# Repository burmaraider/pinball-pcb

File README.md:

# Pinball PCB's - Free to all

# What is this?

These boards are getting hard to find, so they should be availiable for people to build themselves.

## Board List

- A-15430 (10 Opto Board)
- 
- more coming soon...

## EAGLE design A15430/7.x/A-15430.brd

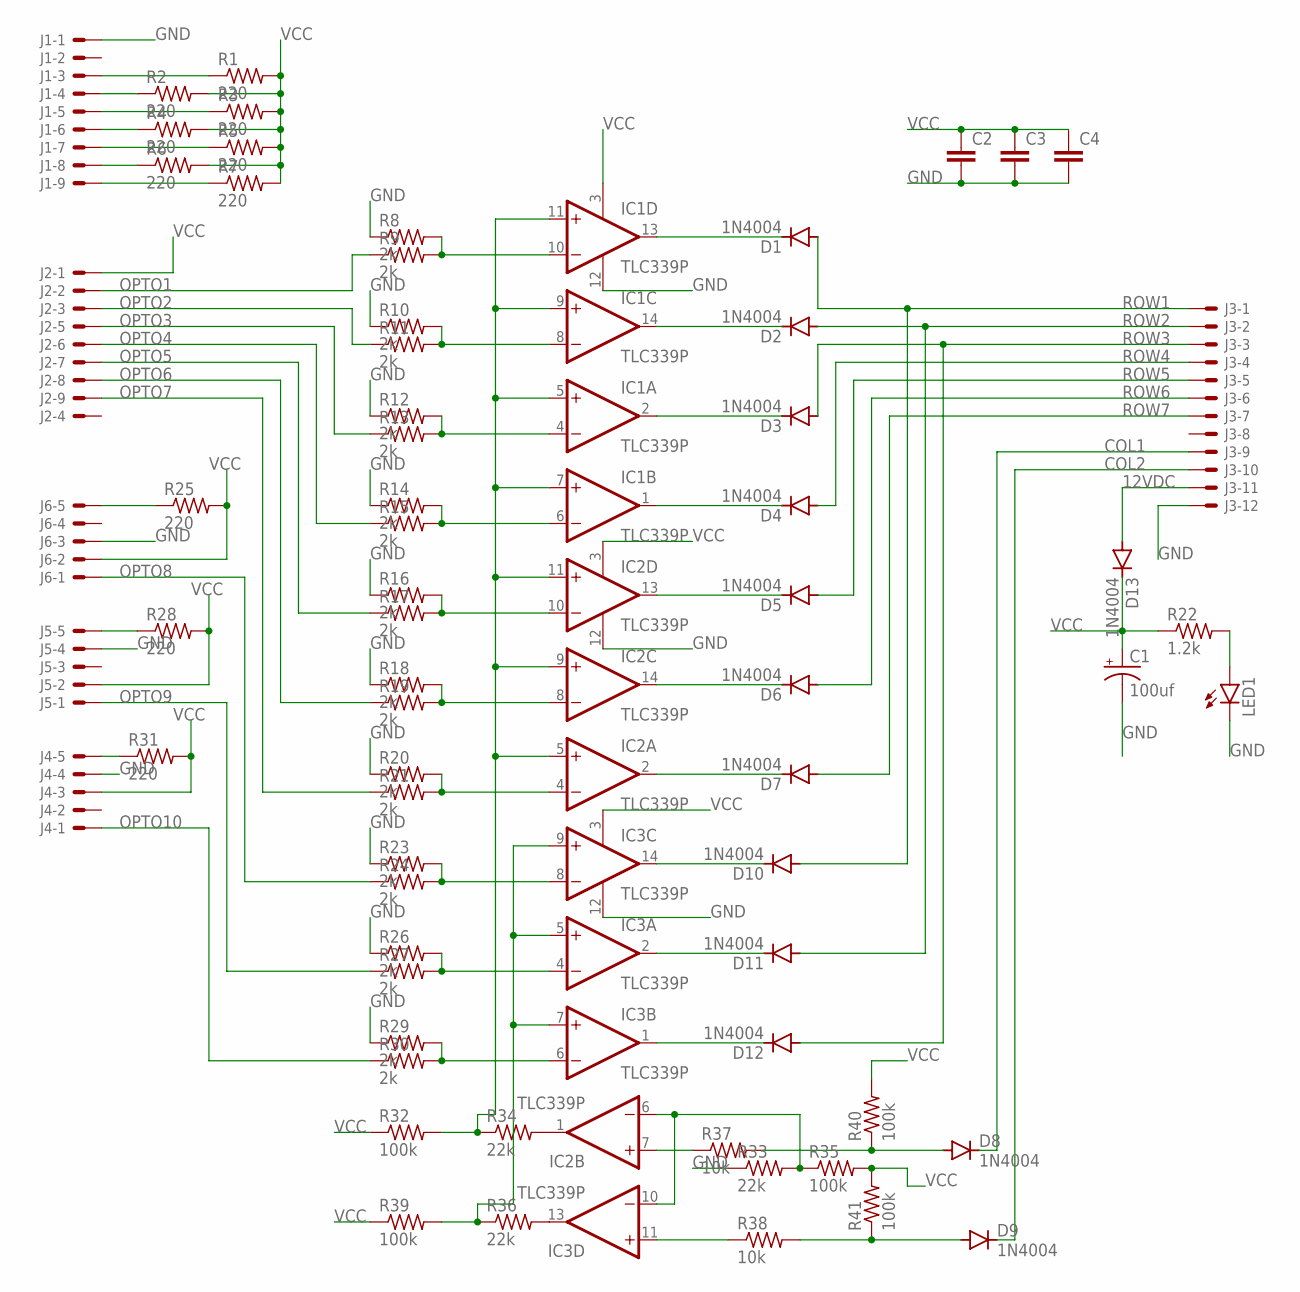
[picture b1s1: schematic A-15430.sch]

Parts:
C1: 100uf; E2,5-5
C2, C3, C4: C2.5/4; C2.5-4
D1, D2, D3, D4, D5, D6, D7, D8, D9, D10, D11, D12, D13: 1N4004; DO41-10
IC1, IC2, IC3: TLC339P; DIL14
J1, J2: KK-156-9
J3: KK-156-12
J4, J5, J6: KK-156-5
LED1: LED5MM
R1, R2, R3, R4, R5, R6, R7, R25, R28, R31: 220; 0617/22
R8, R9, R10, R11, R12, R13, R14, R15, R16, R17, R18, R19, R20, R21, R23, R24, R26, R27, R29, R30: 2k; 0207/10
R22: 1.2k; 0207/10
R32, R35, R39, R40, R41: 100k; 0207/10
R33, R34, R36: 22k; 0207/10
R37, R38: 10k; 0207/10

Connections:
12VDC: D13.A, J3.11
COL1: D8.C, J3.9
COL2: D9.C, J3.10
GND: C1.-, C2.2, C3.2, C4.2, IC1.12 (V-), IC2.12 (V-), IC3.12 (V-), J1.1, J3.12, J4.4, J5.4, J6.3, LED1.K (C), R8.1, R10.1, R12.1, R14.1, R16.1, R18.1, R20.1, R23.1, R26.1, R29.1, R33.1
unnamed: D1.C, IC1.13 (OUT)
unnamed: D2.C, IC1.14 (OUT)
unnamed: D3.C, IC1.2 (OUT)
unnamed: D4.C, IC1.1 (OUT)
unnamed: J6.5, R25.1
unnamed: LED1.A, R22.2
unnamed: J1.3, R1.1
unnamed: D5.C, IC2.13 (OUT)
unnamed: J1.4, R2.1
unnamed: J1.5, R3.1
unnamed: D6.C, IC2.14 (OUT)
unnamed: J1.6, R4.1
unnamed: D7.C, IC2.2 (OUT)
unnamed: J1.7, R5.1
unnamed: J1.8, R6.1
unnamed: IC1.10 (-IN), R8.2, R9.2
unnamed: IC1.8 (-IN), R10.2, R11.2
unnamed: IC1.4 (-IN), R12.2, R13.2
unnamed: IC1.6 (-IN), R14.2, R15.2
unnamed: IC2.10 (-IN), R16.2, R17.2
unnamed: IC2.8 (-IN), R18.2, R19.2
unnamed: IC2.4 (-IN), R20.2, R21.2
unnamed: IC3.8 (-IN), R23.2, R24.2
unnamed: IC3.4 (-IN), R26.2, R27.2
unnamed: IC3.6 (-IN), R29.2, R30.2
unnamed: IC2.6 (-IN), IC3.10 (-IN), R33.2, R35.1
unnamed: D10.C, IC3.14 (OUT)
unnamed: D11.C, IC3.2 (OUT)
unnamed: D12.C, IC3.1 (OUT)
unnamed: J5.5, R28.1
unnamed: IC3.13 (OUT), R36.2
unnamed: IC1.5 (+IN), IC1.7 (+IN), IC1.9 (+IN), IC1.11 (+IN), IC2.5 (+IN), IC2.9 (+IN), IC2.11 (+IN), R32.2, R34.1
unnamed: J4.5, R31.1
unnamed: D9.A, R38.2, R41.1
unnamed: IC3.5 (+IN), IC3.7 (+IN), IC3.9 (+IN), R36.1, R39.2
unnamed: IC3.11 (+IN), R38.1
unnamed: J1.9, R7.1
unnamed: D8.A, R37.2, R40.1
unnamed: IC2.1 (OUT), R34.2
unnamed: IC2.7 (+IN), R37.1
OPTO1: J2.2, R9.1
OPTO2: J2.3, R11.1
OPTO3: J2.5, R13.1
OPTO4: J2.6, R15.1
OPTO5: J2.7, R17.1
OPTO6: J2.8, R19.1
OPTO7: J2.9, R21.1
OPTO8: J6.1, R24.1
OPTO9: J5.1, R27.1
OPTO10: J4.1, R30.1
ROW1: D1.A, D10.A, J3.1
ROW2: D2.A, D11.A, J3.2
ROW3: D3.A, D12.A, J3.3
ROW4: D4.A, J3.4
ROW5: D5.A, J3.5
ROW6: D6.A, J3.6
ROW7: D7.A, J3.7
VCC: C1.+, C2.1, C3.1, C4.1, D13.C, IC1.3 (V+), IC2.3 (V+), IC3.3 (V+), J2.1, J4.3, J5.2, J6.2, R1.2, R2.2, R3.2, R4.2, R5.2, R6.2, R7.2, R22.1, R25.2, R28.2, R31.2, R32.1, R35.2, R39.1, R40.2, R41.2

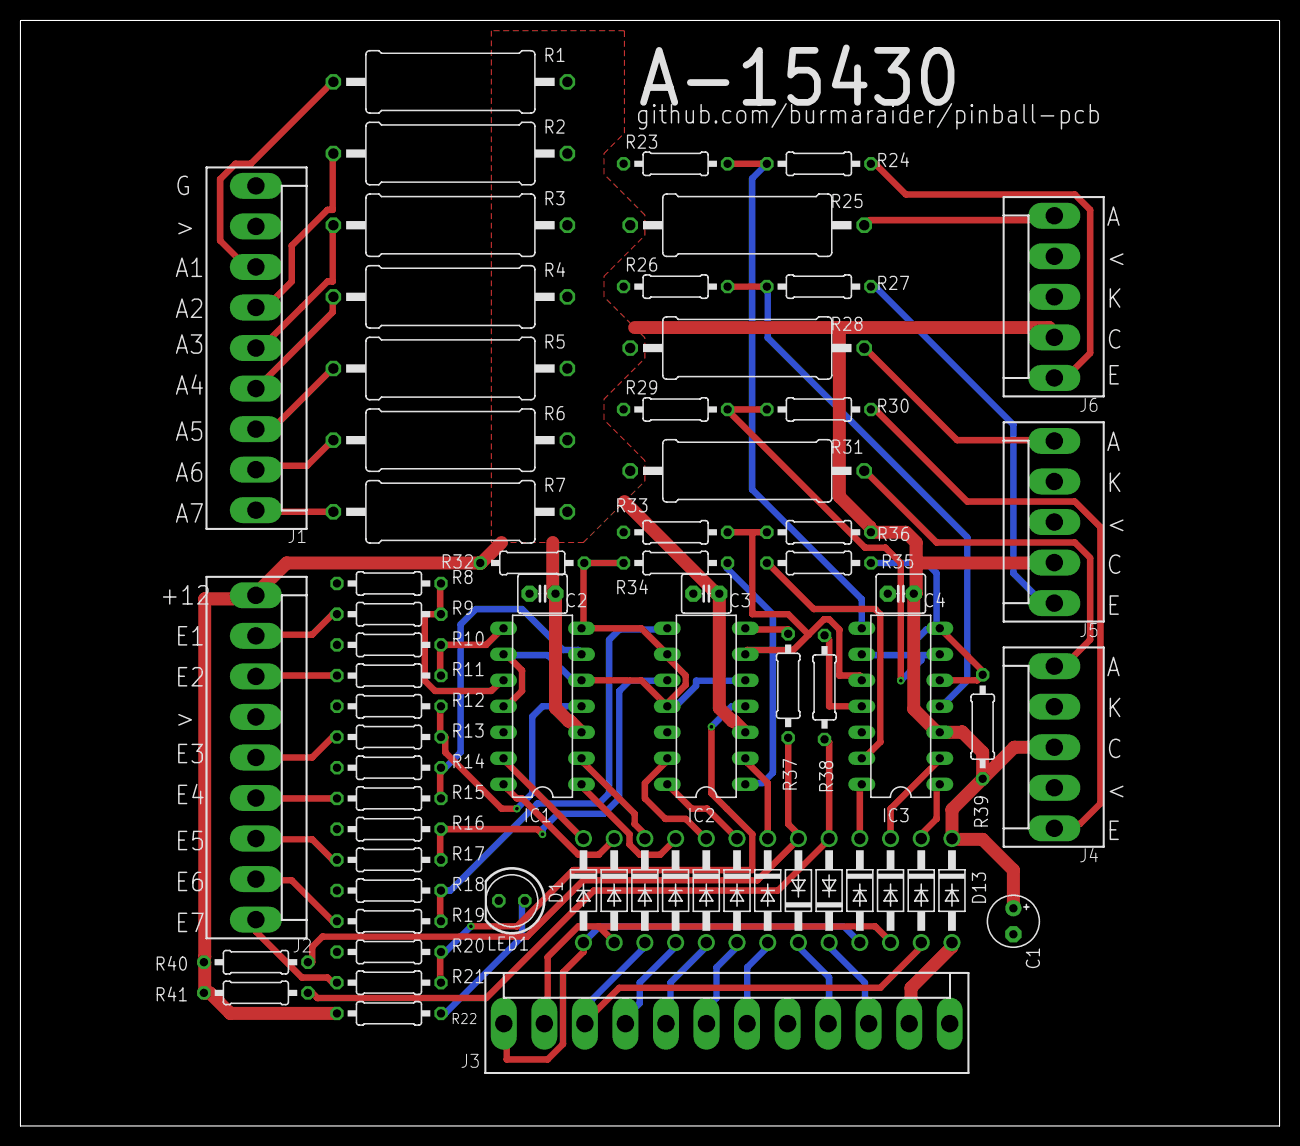
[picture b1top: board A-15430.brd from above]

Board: 2 copper layers, 123.0 x 108.0 mm, 68 parts (0 on the bottom side), 62 nets.

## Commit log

2019-02-18 Reorganized the folder structure
